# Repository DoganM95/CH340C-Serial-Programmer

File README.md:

# Intro

This Module is a specialized ESP32 programmer that simplifies the programming process by incorporating auto-programming functionality. This means there's no need for manual interaction with the ESP32 during programming, such as pressing buttons on the board. Additionally, it supports Power Delivery (PD), allowing the attached ESP32 to be powered from a PD source at 5V.

# Shop

This pcb can now be ordered on etsy:  
<https://etsy.com/de-en/listing/1858636382>

## Visual Overview

<table>
  <tr>
    <td>
      
    </td>
    <td>
      
    </td>
    <td>
      
    </td>
    <td>
      
    </td>
  </tr>
</table>

## Key Features

- **Compact Design**: The module is designed to occupy minimal space, making it ideal for streamlined setups.
- **Power Delivery Support**: Compatible with Power Delivery, enabling the ESP32 to run directly from a 5V PD source.
- **USB-C Connectivity**: Utilizes a USB-C connection for modern, reversible, and reliable connectivity.
- **Auto-Programming**: Simplifies the programming process by eliminating the need for manual button presses on the ESP32 during programming.

## BOM

The parts are listed in the recommended order of soldering.

| Reference | Part Name               | Description                           |
|-----------|-------------------------|---------------------------------------|
| J1        | CQ-USB-C16PSMT01        | 16 Pin female USB C connector         | 
| U2        | CH340C                  | Programming IC, SOP-16 package        |
| R1        | 0603-5.1k               | Resistor, 0603 sized, 5.1 kilo Ohm    |
| R2        | 0603-5.1k               | Resistor, 0603 sized, 5.1 kilo Ohm    |
| C1        | 0603-100nF              | Capacitor, 0603 sized, 100 nano Farad |
| C2        | 0603-4.7uF              | Capacitor, 0603 sized, 4.7 micro Farad |
| JP1       | Jumper                  | short: mid (VCC) with left/inner (3V3) or right/outer (5V)|
| U4        | AO3400                  | N-Channel Mosfet, SOT-23 package      |
| U3        | AO3400                  | N-Channel Mosfet, SOT-23 package      |
| U1        | AMS1117 3.3V            | 5V to 3.3V Voltage regulator, SOT-223 package |

## Driver
https://wch.cn/download/CH341SER_ZIP.html

## Key Takeaways
- The CH340C can be powered with `3.3V` or `5V`. The input Voltage translates to its TX voltage and 5V is too high for e.g. an esp32, so it gets powered with `3.3V` 
- The `3V` pin of the CH340C needs to be connected to `GND` with a `100nF` capacitor, else it will not work and not show up in device manager
- Connecting it with wrong polarity (`5V` and `GND`) gets the chip hot quickly, but doesn't break it when cutting the power off soon (like 20 seconds)
- The minimum circuit, only to check if a CH340C ic is functional, consists of a usb port with (`5V`, `D-`, `D+`, `GND`) connected to the CH340C as well as the said `100nF` capacitor from its `3V` pin to `GND`
- The capacitor (`C2`) between `EN` and `GND` needs to be high enough, else the auto reset will not work. `100nF` was too little, so the IDE was stuck at `Hard resetting via RTS pin...` and the module had to be plugged out and in again manually. Increasing the capacitance to `4.7uF` solved this and the auto reset works fine with that.

## Video preview
https://github.com/DoganM95/CH340C-Pcb/assets/38842553/810827a4-b2fa-454a-bed7-59ae43e08667

## Sponsorship - [PCBWay](https://pcbway.com/g/8bcMJY)
The physical PCB's and stencil are sponsored by [PCBWay](https://pcbway.com/g/8bcMJY).  
Overall i am very satisfied with the quality of the pcb's, especially with
- the matte surface finish
- the cover of the vias, which almost feel like plugged, so there is no way to accidentally put solder in there to cause a short circuit
- the traces, which are covered better than other manufacturers do and cannot be brushed/scraped away easily. Big plus for that

One thing i missed was clearer texts (white) on the pcb's, but printing those in good quality, especially sized at 0.6mm, can be challenging.  
I am very pleased to get these sponsored by [PCBWay](https://pcbway.com/g/8bcMJY) and can recommend their service, especially for the high quality you get and the huge amount of configurable settings.

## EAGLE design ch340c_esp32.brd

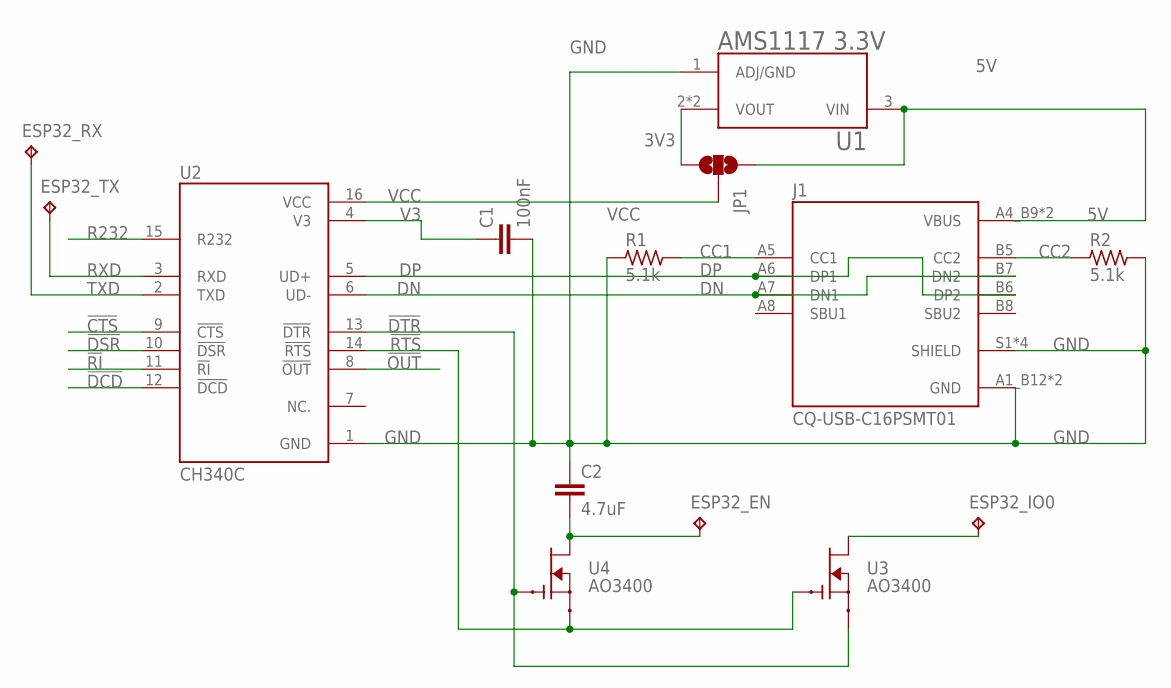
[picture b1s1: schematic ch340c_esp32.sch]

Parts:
C1: 100nF; C0603
C2: 4.7uF; C0603
ESP32_EN, ESP32_IO0, ESP32_RX, ESP32_TX: TPB1,27; B1,27
J1: CQ-USB-C16PSMT01; SHENZHEN-CHUANGQIN-TECHNOLOGY_CQ-USB-C16PSMT01
JP1: JUMPER-SMT_3_NO_NO-SILK; SMT-JUMPER_3_NO_NO-SILK
R1, R2: 5.1k; RC-MASTER-SMD_R0603MP
U1: AMS1117 3.3V; SOT229P700X180-4N
U2: CH340C; SOIC127P600X180-16N
U3, U4: AO3400; SOT23

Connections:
3V3: JP1.1, U1.2 (VOUT), U1.4 (VOUT)
5V: J1.A4_B9 (VBUS), J1.B4_A9 (VBUS), JP1.3, U1.3 (VIN)
!CTS: U2.9 (!CTS)
!DCD: U2.12 (!DCD)
!DSR: U2.10 (!DSR)
!DTR: U2.13 (!DTR), U3.2 (S), U4.1 (G)
!OUT: U2.8 (!OUT)
!RI: U2.11 (!RI)
!RTS: U2.14 (!RTS), U3.1 (G), U4.2 (S)
CC1: J1.A5 (CC1), R1.2
CC2: J1.B5 (CC2), R2.1
DN: J1.A7 (DN1), J1.B7 (DN2), U2.6 (UD-)
DP: J1.A6 (DP1), J1.B6 (DP2), U2.5 (UD+)
EN: C2.2, ESP32_EN.TP, U4.3 (D)
GND: C1.2, C2.1, J1.A1_B12 (GND), J1.B1_A12 (GND), J1.S1 (SHIELD), J1.S2 (SHIELD), J1.S3 (SHIELD), J1.S4 (SHIELD), R1.1, R2.2, U1.1 (ADJ/GND), U2.1 (GND)
IO0: ESP32_IO0.TP, U3.3 (D)
R232: U2.15 (R232)
RXD: ESP32_TX.TP, U2.3 (RXD)
TXD: ESP32_RX.TP, U2.2 (TXD)
V3: C1.1, U2.4 (V3)
VCC: JP1.2, U2.16 (VCC)

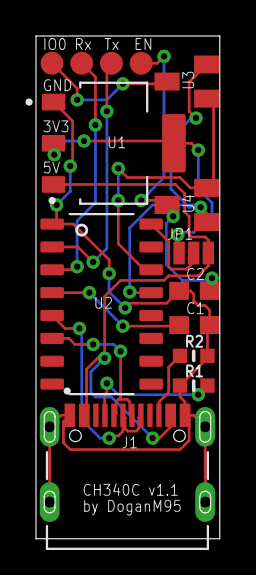
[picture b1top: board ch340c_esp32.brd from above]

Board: 2 copper layers, 10.2 x 27.9 mm, 14 parts (0 on the bottom side), 15 nets.

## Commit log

2023-11-14 init
2023-11-14 add unrouted preview
2023-11-14 Create LICENSE
2023-11-15 resolve issues
2023-11-28 prototype v1.1
2023-11-29 route airwires for v1.1
2023-11-29 Update BOM
2023-12-08 add images of real product
2023-12-08 fix BOM
2023-12-08 add sponsorship
2023-12-08 reformat code for better readability
2023-12-08 update C2 cap value
2023-12-12 quick schematic cleanup
2023-12-12 add schematic
2024-04-22 optimize schematic

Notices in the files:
parts and their libraries:
SparkFun-Jumpers: Licensing: Creative Commons ShareAlike 4.0 International - https://creativecommons.org/licenses/by-sa/4.0
